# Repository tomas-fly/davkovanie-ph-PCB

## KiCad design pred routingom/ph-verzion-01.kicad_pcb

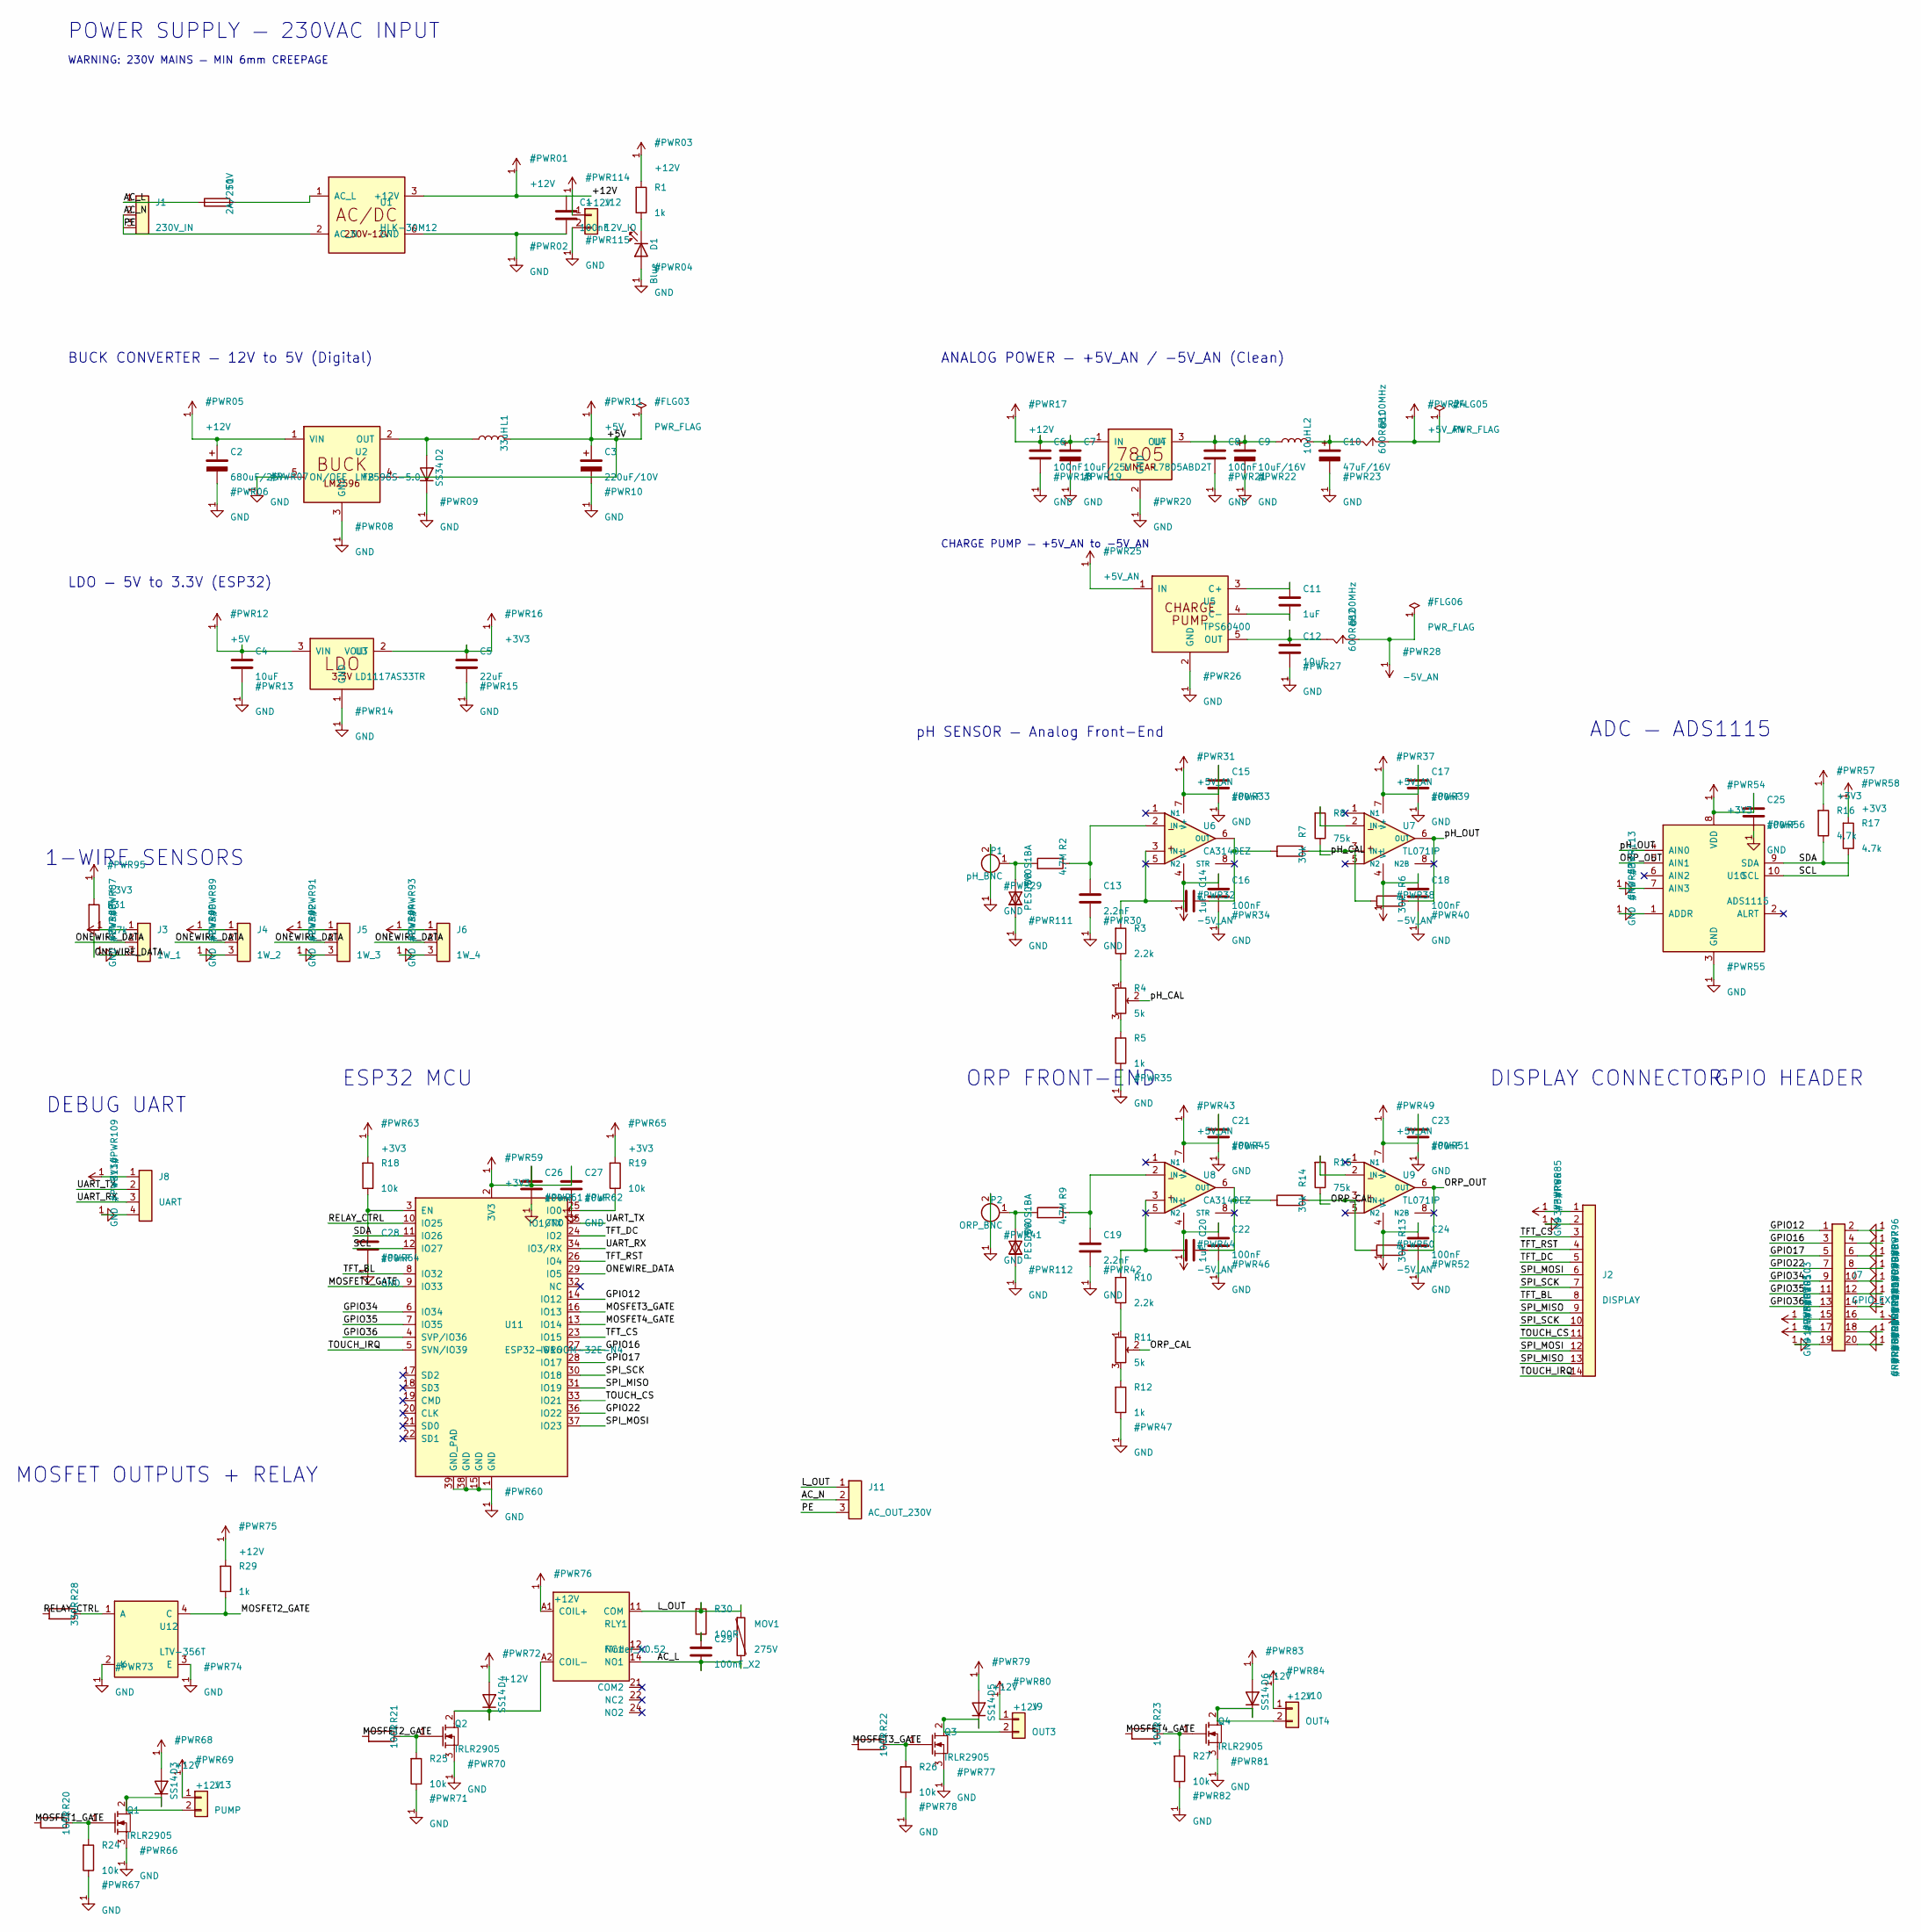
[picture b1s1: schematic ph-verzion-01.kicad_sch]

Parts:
C1, C6, C8, C15, C16, C17, C18, C21, C22, C23, C24, C25, C26, C28: 100nF; C_0805_2012Metric
C2: 680uF/25V; CP_Radial_D10.0mm_P5.00mm
C3: 220uF/10V; CP_Radial_D8.0mm_P3.50mm
C4, C12, C27: 10uF; C_0805_2012Metric
C5: 22uF; C_1206_3216Metric
C7: 10uF/25V; CP_Radial_D6.3mm_P2.50mm
C9: 10uF/16V; CP_Radial_D6.3mm_P2.50mm
C10: 47uF/16V; CP_Radial_D6.3mm_P2.50mm
C11, C14, C20: 1uF; C_0805_2012Metric
C13, C19: 2.2nF; C_0805_2012Metric
C29: 100nF_X2; C_Rect_L18.0mm_W5.0mm_P15.00mm_FKS3_FKP3
D1: Blue; LED_0805_2012Metric
D2: SS34; D_SMC
D3, D4, D5, D6: SS14; D_SMA
D8, D9: PESD5V0S1BA; D_SOD-323
F1: 2A/250V; Fuseholder_Cylinder-5x20mm_Schurter_FPG4_Vertical_Closed
FB1, FB2: 600R@100MHz; L_0805_2012Metric
J1: 230V_IN; TerminalBlock_Phoenix_MKDS-1,5-3-5.08_1x03_P5.08mm_Horizont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
J2: DISPLAY; PinHeader_1x14_P2.54mm_Vertical
J3: 1W_1; JST_XH_B3B-XH-A_1x03_P2.50mm_Vertical
J4: 1W_2; JST_XH_B3B-XH-A_1x03_P2.50mm_Vertical
J5: 1W_3; JST_XH_B3B-XH-A_1x03_P2.50mm_Vertical
J6: 1W_4; JST_XH_B3B-XH-A_1x03_P2.50mm_Vertical
J7: GPIO_EXT; PinHeader_2x10_P2.54mm_Vertical
J8: UART; PinHeader_1x04_P2.54mm_Vertical
J9: OUT3; TerminalBlock_Phoenix_MKDS-1,5-2-5.08_1x02_P5.08mm_Horizont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
J10: OUT4; TerminalBlock_Phoenix_MKDS-1,5-2-5.08_1x02_P5.08mm_Horizont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
J11: AC_OUT_230V; TerminalBlock_Phoenix_MKDS-1,5-3-5.08_1x03_P5.08mm_Horizont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
J12: 12V_IO; TerminalBlock_Phoenix_MKDS-1,5-2-5.08_1x02_P5.08mm_Horizont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
J13: PUMP; TerminalBlock_Phoenix_MKDS-1,5-2-5.08_1x02_P5.08mm_Horizont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
L1: 33uH; L_Bourns-SRN1060
L2: 10uH; L_0805_2012Metric
MOV1: 275V; RV_Disc_D12mm_W4.2mm_P7.5mm
P1: pH_BNC; BNC_Amphenol_B6252HB-NPP3G-50_Horizontal
P2: ORP_BNC; BNC_Amphenol_B6252HB-NPP3G-50_Horizontal
Q1, Q2, Q3, Q4: IRLR2905; TO-252-2
R1, R5, R12, R29: 1k; R_0805_2012Metric
R2, R9: 4.7M; R_0805_2012Metric
R3, R10: 2.2k; R_0805_2012Metric
R4, R11: 5k; Potentiometer_Bourns_3214W_Vertical
R6, R7, R13, R14: 30k; R_0805_2012Metric
R8, R15: 75k; R_0805_2012Metric
R16, R17, R31: 4.7k; R_0805_2012Metric
R18, R19, R24, R25, R26, R27: 10k; R_0805_2012Metric
R20, R21, R22, R23, R30: 100R; R_0805_2012Metric
R28: 330R; R_0805_2012Metric
RLY1: Finder_40.52; Relay_DPDT_Finder_40.52
U1: HLK-30M12; Converter_ACDC_Hi-Link_HLK-30Mxx
U2: LM2596S-5.0; TO-263-5_TabPin3
U3: LD1117AS33TR; SOT-223-3_TabPin2
U4: L7805ABD2T; TO-263-2
U5: TPS60400; SOT-23-5
U6, U8: CA3140EZ; SOIC-8_3.9x4.9mm_P1.27mm
U7, U9: TL071IP; SOIC-8_3.9x4.9mm_P1.27mm
U10: ADS1115; MSOP-10_3x3mm_P0.5mm
U11: ESP32-WROOM-32E-N4; ESP32-WROOM-32E
U12: LTV-356T; SOP-4_3.8x4.1mm_P2.54mm

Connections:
+3V3: C5.1, C25.1, C26.1, C27.1, J2.1, J3.1, J4.1, J5.1, J6.1, J7.15, J8.1, R16.1, R17.1, R18.1, R19.1, R31.1, U3.2 (VOUT), U10.8 (VDD), U11.2 (3V3)
+5V: C3.1, C4.1, J7.16, L1.2, U2.4 (FB), U3.3 (VIN)
+5V_AN: C15.1, C17.1, C21.1, C23.1, FB1.2, U5.1 (IN), U6.7 (V+), U7.7 (V+), U8.7 (V+), U9.7 (V+)
+12V: C1.1, C2.1, C6.1, C7.1, D3.2 (A), D4.2 (A), D5.2 (A), D6.2 (A), J7.17, J9.1, J10.1, J12.1, J13.1, R1.1, R29.1, RLY1.A1 (COIL+), U1.3 (+12V), U2.1 (VIN), U4.1 (IN)
-5V_AN: C16.1, C18.1, C22.1, C24.1, FB2.2, U6.4 (V-), U7.4 (V-), U8.4 (V-), U9.4 (V-)
/AC_L: C29.2, F1.1, J1.1, MOV1.2, RLY1.14 (NO1)
/GPIO12: J7.1, U11.14 (IO12)
/GPIO16: J7.3, U11.27 (IO16)
/GPIO17: J7.5, U11.28 (IO17)
/GPIO22: J7.7, U11.36 (IO22)
/GPIO34: J7.9, U11.6 (IO34)
/GPIO35: J7.11, U11.7 (IO35)
/GPIO36: J7.13, U11.4 (SVP/IO36)
/L_OUT: J11.1, MOV1.1, R30.1, RLY1.11 (COM)
/MOSFET1_GATE: R20.1, U11.9 (IO33)
/MOSFET2_GATE: R21.1, R29.2, U12.4 (C)
/MOSFET3_GATE: R22.1, U11.16 (IO13)
/MOSFET4_GATE: R23.1, U11.13 (IO14)
/ONEWIRE_DATA: J3.2, J4.2, J5.2, J6.2, R31.2, U11.29 (IO5)
/ORP_CAL: R11.2, R15.2
/ORP_OUT: R13.2, U9.6 (OUT), U10.5 (AIN1)
/RELAY_CTRL: R28.1, U11.10 (IO25)
/SCL: R17.2, U10.10 (SCL), U11.12 (IO27)
/SDA: R16.2, U10.9 (SDA), U11.11 (IO26)
/SPI_MISO: J2.9, J2.13, U11.31 (IO19)
/SPI_MOSI: J2.6, J2.12, U11.37 (IO23)
/SPI_SCK: J2.7, J2.10, U11.30 (IO18)
/TFT_BL: J2.8, U11.8 (IO32)
/TFT_CS: J2.3, U11.23 (IO15)
/TFT_DC: J2.5, U11.24 (IO2)
/TFT_RST: J2.4, U11.26 (IO4)
/TOUCH_CS: J2.11, U11.33 (IO21)
/TOUCH_IRQ: J2.14, U11.5 (SVN/IO39)
/UART_RX: J8.3, U11.34 (IO3/RX)
/UART_TX: J8.2, U11.35 (IO1/TX)
/pH_CAL: R4.2, R8.2
/pH_OUT: R6.2, U7.6 (OUT), U10.4 (AIN0)
GND: C1.2, C2.2, C3.2, C4.2, C5.2, C6.2, C7.2, C8.2, C9.2, C10.2, C12.2, C13.2, C15.2, C16.2, C17.2, C18.2, C19.2, C21.2, C22.2, C23.2, C24.2, C25.2, C26.2, C27.2, C28.2, D1.2 (A), D2.1 (K), D8.1 (A1), D9.1 (A1), J2.2, J3.3, J4.3, J5.3, J6.3, J7.2, J7.4, J7.6, J7.8, J7.10, J7.12, J7.14, J7.18, J7.19, J7.20, J8.4, J12.2, P1.2 (Shield), P2.2 (Shield), Q1.3 (S), Q2.3 (S), Q3.3 (S), Q4.3 (S), R5.2, R12.2, R24.2, R25.2, R26.2, R27.2, U1.6 (GND), U2.3 (GND), U2.5 (ON/OFF), U3.1 (GND), U4.2 (GND), U5.2 (GND), U10.1 (ADDR), U10.3 (GND), U10.7 (AIN3), U11.1 (GND), U11.15 (GND), U11.38 (GND), U11.39 (GND_PAD), U12.2 (K), U12.3 (E)
unnamed: C10.1, FB1.1, L2.2
unnamed: C29.1, R30.2
unnamed: D1.1 (K), R1.2
unnamed: D2.2 (A), L1.1, U2.2 (OUT)
unnamed: D3.1 (K), J13.2, Q1.2 (D)
unnamed: D4.1 (K), Q2.2 (D), RLY1.A2 (COIL-)
unnamed: D5.1 (K), J9.2, Q3.2 (D)
unnamed: D6.1 (K), J10.2, Q4.2 (D)
unnamed: D8.2 (A2), P1.1 (Signal), R2.1
unnamed: D9.2 (A2), P2.1 (Signal), R9.1
unnamed: Q1.1 (G), R20.2, R24.1
unnamed: Q2.1 (G), R21.2, R25.1
unnamed: Q3.1 (G), R22.2, R26.1
unnamed: Q4.1 (G), R23.2, R27.1
unnamed: R3.2, R4.1
unnamed: R4.3, R5.1
unnamed: R10.2, R11.1
unnamed: R11.3, R12.1
unnamed: F1.2, U1.1 (AC_L)
unnamed: C8.1, C9.1, L2.1, U4.3 (OUT)
unnamed: C11.1, U5.3 (C+)
unnamed: C11.2, U5.4 (C-)
unnamed: C12.1, FB2.1, U5.5 (OUT)
unnamed: C14.1, R3.1, U6.3 (IN+)
unnamed: C13.1, R2.2, U6.2 (IN-)
unnamed: C14.2, R7.1, U6.6 (OUT)
unnamed: R6.1, R7.2, U7.3 (IN+)
unnamed: R8.1, U7.2 (IN-)
unnamed: C20.1, R10.1, U8.3 (IN+)
unnamed: C19.1, R9.2, U8.2 (IN-)
unnamed: C20.2, R14.1, U8.6 (OUT)
unnamed: R13.1, R14.2, U9.3 (IN+)
unnamed: R15.1, U9.2 (IN-)
unnamed: C28.1, R18.2, U11.3 (EN)
unnamed: R19.2, U11.25 (IO0)
unnamed: R28.2, U12.1 (A)

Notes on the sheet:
DEBUG UART
DISPLAY CONNECTOR
1-WIRE SENSORS
BUCK CONVERTER — 12V to 5V (Digital)
ANALOG POWER — +5V_AN / -5V_AN (Clean)
WARNING: 230V MAINS — MIN 6mm CREEPAGE
GPIO HEADER
CHARGE PUMP — +5V_AN to -5V_AN
ESP32 MCU
ADC — ADS1115
MOSFET OUTPUTS + RELAY
LDO — 5V to 3.3V (ESP32)
POWER SUPPLY — 230VAC INPUT
pH SENSOR — Analog Front-End
ORP FRONT-END

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
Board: 2 copper layers, 106 parts (0 on the bottom side), 76 nets, no tracks yet.

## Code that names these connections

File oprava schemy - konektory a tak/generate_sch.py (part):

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  )"""

# HLK-30M12 custom symbol: AC-DC module
# Pins: 1=AC_L, 2=AC_N, 3=+12V, 4=GND
LIB_HLK_30M12 = """(symbol "Custom:HLK-30M12" (pin_names (offset 1.016))
    (exclude_from_sim no) (in_bom yes) (on_board yes)
    (property "Reference" "U" (at 0 8.89 0)
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                               40, 65, 0, pin_count=3))

    # Labels on connector pins
    labels.append(make_label("AC_L", 36.19, 62.46))
    labels.append(make_label("AC_N", 36.19, 65))
    labels.append(make_label("PE", 36.19, 67.54))

    # F1: Fuse (vertical) — between connector L and HLK AC_L
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
    # F1 pin 2 exits at (58.81, 62.46)
    # HLK-30M12 at (85, 65)
    # HLK AC_L pin at (-11.43 from center + 3.81 up) = (85-11.43, 65-3.81) = (73.57, 61.19)
    # Wait, pin is at (at -11.43 3.81 0) meaning offset from symbol center
    # So AC_L absolute: (85-11.43, 65-3.81) = (73.57, 61.19)
    # AC_N absolute: (85-11.43, 65+3.81) = (73.57, 68.81)
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    symbols.append(make_symbol("Custom:HLK-30M12", "U1", "HLK-30M12",
                               85, 65, 0, pin_numbers=["1", "2", "3", "6"]))

    # Wire: F1 pin 2 → HLK AC_L
    wires.append(make_wire(58.81, 62.46, 73.57, 62.46))
    wires.append(make_wire(73.57, 62.46, 73.57, 61.19))

    # Wire: J1 pin 2 (N) → HLK AC_N
    wires.append(make_wire(36.19, 65, 36.19, 68.81))
    wires.append(make_wire(36.19, 68.81, 73.57, 68.81))

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                               r5_x, r5_y + 8, 0, pin_count=1))
    wires.append(make_wire(r5_x, r5_y + 3.81, r5_x, r5_y + 8))

    # Pot wiper (pin2) at (r4_x + 3.81, r4_y) → pH_CAL label (offset calibration)
    labels.append(make_label("pH_CAL", r4_x + 3.81 + 2, r4_y))
    wires.append(make_wire(r4_x + 3.81, r4_y, r4_x + 3.81 + 10, r4_y))

    # ======== U7: TL071IP (output stage, inverting amplifier) ========
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    wires.append(make_wire(r8_x, r8_y - 3.81, r8_x, u7_pin3_y))
    wires.append(make_wire(r8_x, u7_pin3_y, u7_pin3_x, u7_pin3_y))

    # R8 bottom → pH_CAL (connected to R4 wiper via net label)
    labels.append(make_label("pH_CAL", r8_x + 2, r8_y + 3.81 + 2))
    wires.append(make_wire(r8_x, r8_y + 3.81, r8_x, r8_y + 3.81 + 2))
    wires.append(make_wire(r8_x, r8_y + 3.81 + 2, r8_x + 10, r8_y + 3.81 + 2))

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    no_connects.append(make_no_connect(u7_pin5_x, u7_pin5_y))
    no_connects.append(make_no_connect(u7_pin8_x, u7_pin8_y))

    # ======== OUTPUT: pH_OUT label ========
    labels.append(make_label("pH_OUT", u7_pin6_x + 2, u7_pin6_y))
    wires.append(make_wire(u7_pin6_x, u7_pin6_y, u7_pin6_x + 15, u7_pin6_y))

    return lib_symbols, symbols, wires, junctions, labels, texts, no_connects
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                               r12_x, r12_y + 8, 0, pin_count=1))
    wires.append(make_wire(r12_x, r12_y + 3.81, r12_x, r12_y + 8))

    # Pot R11 wiper (pin2) at (r11_x + 3.81, r11_y) → ORP_CAL label (offset calibration)
    labels.append(make_label("ORP_CAL", r11_x + 3.81 + 2, r11_y))
    wires.append(make_wire(r11_x + 3.81, r11_y, r11_x + 3.81 + 10, r11_y))

    # ======== U9: TL071IP (inverting amplifier) ========
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    wires.append(make_wire(r15_x, r15_y - 3.81, r15_x, u9_pin3_y))
    wires.append(make_wire(r15_x, u9_pin3_y, u9_pin3_x, u9_pin3_y))

    # R15 bottom → ORP_CAL (connected to R11 wiper via net label)
    labels.append(make_label("ORP_CAL", r15_x + 2, r15_y + 3.81 + 2))
    wires.append(make_wire(r15_x, r15_y + 3.81, r15_x, r15_y + 3.81 + 2))
    wires.append(make_wire(r15_x, r15_y + 3.81 + 2, r15_x + 10, r15_y + 3.81 + 2))

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    no_connects.append(make_no_connect(u9_pin5_x, u9_pin5_y))
    no_connects.append(make_no_connect(u9_pin8_x, u9_pin8_y))

    # ======== OUTPUT: ORP_OUT label ========
    labels.append(make_label("ORP_OUT", u9_pin6_x + 2, u9_pin6_y))
    wires.append(make_wire(u9_pin6_x, u9_pin6_y, u9_pin6_x + 15, u9_pin6_y))

    return lib_symbols, symbols, wires, junctions, labels, texts, no_connects
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    scl_x, scl_y   = u10_x + 13.97, u10_y - 2.54   # (368.97, 197.46)
    alrt_x, alrt_y = u10_x + 13.97, u10_y + 5.08   # (368.97, 205.08)

    # AIN0 ← pH_OUT (net label)
    labels.append(make_label("pH_OUT", ain0_x - 5, ain0_y, angle=180))
    wires.append(make_wire(ain0_x - 5, ain0_y, ain0_x, ain0_y))

    # AIN1 ← ORP_OUT (net label)
    labels.append(make_label("ORP_OUT", ain1_x - 5, ain1_y, angle=180))
    wires.append(make_wire(ain1_x - 5, ain1_y, ain1_x, ain1_y))

    # AIN2 — no connect (voľný)
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    lbl_offset = 5  # wire length from pin to label

    # IO1/TX → UART_TX
    labels.append(make_label("UART_TX", rx + lbl_offset, io1_y))
    wires.append(make_wire(rx, io1_y, rx + lbl_offset + 10, io1_y))

    # IO2 → TFT_DC
    labels.append(make_label("TFT_DC", rx + lbl_offset, io2_y))
    wires.append(make_wire(rx, io2_y, rx + lbl_offset + 10, io2_y))

    # IO3/RX → UART_RX
    labels.append(make_label("UART_RX", rx + lbl_offset, io3_y))
    wires.append(make_wire(rx, io3_y, rx + lbl_offset + 10, io3_y))

    # IO4 → TFT_RST
    labels.append(make_label("TFT_RST", rx + lbl_offset, io4_y))
    wires.append(make_wire(rx, io4_y, rx + lbl_offset + 10, io4_y))

    # IO5 → ONEWIRE_DATA
    labels.append(make_label("ONEWIRE_DATA", rx + lbl_offset, io5_y))
    wires.append(make_wire(rx, io5_y, rx + lbl_offset + 10, io5_y))

    # IO12 → voľný (J7) — no label needed, will be in step 10
    labels.append(make_label("GPIO12", rx + lbl_offset, io12_y))
    wires.append(make_wire(rx, io12_y, rx + lbl_offset + 10, io12_y))

    # IO13 → MOSFET3_GATE
    labels.append(make_label("MOSFET3_GATE", rx + lbl_offset, io13_y))
    wires.append(make_wire(rx, io13_y, rx + lbl_offset + 10, io13_y))

    # IO14 → MOSFET4_GATE
    labels.append(make_label("MOSFET4_GATE", rx + lbl_offset, io14_y))
    wires.append(make_wire(rx, io14_y, rx + lbl_offset + 10, io14_y))

    # IO15 → TFT_CS
    labels.append(make_label("TFT_CS", rx + lbl_offset, io15_y))
    wires.append(make_wire(rx, io15_y, rx + lbl_offset + 10, io15_y))

    # IO16 → voľný (J7)
    labels.append(make_label("GPIO16", rx + lbl_offset, io16_y))
    wires.append(make_wire(rx, io16_y, rx + lbl_offset + 10, io16_y))

    # IO17 → voľný (J7)
    labels.append(make_label("GPIO17", rx + lbl_offset, io17_y))
    wires.append(make_wire(rx, io17_y, rx + lbl_offset + 10, io17_y))

    # IO18 → SPI_SCK
    labels.append(make_label("SPI_SCK", rx + lbl_offset, io18_y))
    wires.append(make_wire(rx, io18_y, rx + lbl_offset + 10, io18_y))

    # IO19 → SPI_MISO
    labels.append(make_label("SPI_MISO", rx + lbl_offset, io19_y))
    wires.append(make_wire(rx, io19_y, rx + lbl_offset + 10, io19_y))

    # IO21 → TOUCH_CS
    labels.append(make_label("TOUCH_CS", rx + lbl_offset, io21_y))
    wires.append(make_wire(rx, io21_y, rx + lbl_offset + 10, io21_y))

    # IO22 → voľný (J7)
    labels.append(make_label("GPIO22", rx + lbl_offset, io22_y))
    wires.append(make_wire(rx, io22_y, rx + lbl_offset + 10, io22_y))

    # IO23 → SPI_MOSI
    labels.append(make_label("SPI_MOSI", rx + lbl_offset, io23_y))
    wires.append(make_wire(rx, io23_y, rx + lbl_offset + 10, io23_y))

    # ======== GPIO net labels (left side) ========
    # IO25 → RELAY_CTRL
    labels.append(make_label("RELAY_CTRL", lx - 15, io25_y, angle=180))
    wires.append(make_wire(lx - 15, io25_y, lx, io25_y))

    # IO26 → SDA
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    wires.append(make_wire(lx - 10, io27_y, lx, io27_y))

    # IO32 → TFT_BL
    labels.append(make_label("TFT_BL", lx - 12, io32_y, angle=180))
    wires.append(make_wire(lx - 12, io32_y, lx, io32_y))

    # IO33 → MOSFET1_GATE
    labels.append(make_label("MOSFET1_GATE", lx - 15, io33_y, angle=180))
    wires.append(make_wire(lx - 15, io33_y, lx, io33_y))

    # IO34 → voľný (J7, input only)
    labels.append(make_label("GPIO34", lx - 12, io34_y, angle=180))
    wires.append(make_wire(lx - 12, io34_y, lx, io34_y))

    # IO35 → voľný (J7, input only)
    labels.append(make_label("GPIO35", lx - 12, io35_y, angle=180))
    wires.append(make_wire(lx - 12, io35_y, lx, io35_y))

    # IO36/SVP → voľný (J7, input only)
    labels.append(make_label("GPIO36", lx - 12, io36_y, angle=180))
    wires.append(make_wire(lx - 12, io36_y, lx, io36_y))

    # IO39/SVN → TOUCH_IRQ
    labels.append(make_label("TOUCH_IRQ", lx - 15, io39_y, angle=180))
    wires.append(make_wire(lx - 15, io39_y, lx, io39_y))

    # ======== Unused SD card pins (left side) — no_connect ========
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        return drain_x, drain_y

    # ================================================================
    # Q1: Pump (MOSFET1_GATE, GPIO33) + J13
    # ================================================================
    q1_x, q1_y = 40, 370
    q1_drain_x, q1_drain_y = mosfet_channel(
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    symbols.append(make_symbol("Device:R", "R28", "330R",
                               r28_x, opto_a_y, 90, pin_count=2))
    wires.append(make_wire(r28_x + 3.81, opto_a_y, opto_a_x, opto_a_y))
    labels.append(make_label("RELAY_CTRL", r28_x - 3.81, opto_a_y, angle=180))

    # Cathode → GND
    symbols.append(make_symbol("power:GND", "#PWR73", "GND",
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    wires.append(make_wire(r29_x, r29_y - 3.81, r29_x, r29_y - 8))

    # Collector → MOSFET2_GATE
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
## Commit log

2026-06-09 jedit
2026-06-10 backup-y
2026-06-10 vyhodenie lck suborov
2026-06-10 nahrada za smd
2026-06-11 opravy schemy
2026-06-11 uprava dosky pred routingom
